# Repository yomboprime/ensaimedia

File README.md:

# Ensaimedia

Ensaimedia permite ver la salida de vídeo de un ZX-Uno o otra FPGA en un ordenador con USB host. Adicionalmente permite redireccionar el teclado, ratón y gamepads del host al ZX-Uno vía puerto serie. La salida de sonido del ZX-Uno también es capturada por el host si dispone de entrada de MIC o de línea de audio. La visualización se realiza desde el navegador web, ya sea en el host, o en otro dispositivo remoto. Por último, permite capturar vídeo y audio a disco.

El desarrollo de este addon ha sido posible gracias a la información y software de Wolfgang Wieser sobre el chip Cypress FX2 [en este sitio web.](https://www.triplespark.net/elec/periph/USB-FX2)

# Índice

En este README:
- [Guía de usuario](https://github.com/yomboprime/ensaimedia#guia-de-usuario-de-ensaimedia)
- [Documentación del protocolo](https://github.com/yomboprime/ensaimedia#documentaci%C3%B3n-ensaimedia)

En este repositorio:
- [Binarios de los cores](https://github.com/yomboprime/ensaimedia/tree/master/cores/)
- [Esquemático y PCB (en formato Kicad)](https://github.com/yomboprime/ensaimedia/tree/master/ensaimediaBoard)
- [Esquemático en formato PDF](https://github.com/yomboprime/ensaimedia/tree/master/ensaimediaBoard/ensaimedia.pdf)
- [Código del servidor](https://github.com/yomboprime/ensaimedia/blob/master/server.js)
- [Código del cliente](https://github.com/yomboprime/ensaimedia/blob/master/client/src/client.js)

# Guia de usuario de Ensaimedia

## Requisitos en el ZX-Uno

Necesitas el addon de Ensaimedia para tu FPGA, así como instalar el core de Ensaimedia de tu máquina retro.

Actualmente sólo está disponible el core oficial de ZX-Uno para ZX Spectrum.

## Requisitos del software Ensaimedia del host:

El host debe ser un sistema Unix, debido a que se usa el programa [fx2pipe](https://www.triplespark.net/elec/periph/USB-FX2/software/fx2pipe.html) para la entrada de vídeo por USB. El cliente (o clientes) puede ser cualquier sistema con un navegador web moderno.

- Ejecuta lo siguiente para instalar los requisitos previos:

`sudo apt install git npm libusb-dev build-essential`

- Pon a tu usuario en el grupo dialout para poder acceder al puerto serie:

`sudo adduser <nombre_de_usuario> dialout`

(Necesitas salir de la sesión o reiniciar para aplicar la adición al grupo, pero puedes reiniciar al terminar la instalación)

## Instalación del software Ensaimedia

Ve al directorio que se desea contenga el directorio de Ensaimedia.

Ejecuta:

```
git clone https://github.com/yomboprime/ensaimedia.git
cd ensaimedia
npm install
```

Adicionalmente hay que instalar unas reglas UDEV. Para ello ejecuta lo siguiente desde el directorio de Ensaimedia:

`sudo cp ./udevrules/z70_usbfx2.rules /etc/udev/rules.d`

Despues reinicia.

## Configuración del software

Edita el fichero `EnsaimediaConfig.json` que está en la raíz de la aplicación:

Como mínimo querrás cambiar el puerto TCP en el que sirve Ensaimedia (opción `listenPort`)

La ruta del fichero del puerto serie se cambia en la opción `serialPortFilePath`.

Si vas a usar audio necesitas primero identificar el dispositivo de audio de tu tarjeta de sonido. Para ello ejecuta:

`arecord -L`

Y verás una lista de dispositivos de entrada de audio. Tendrás que ir probando hasta dar con el mejor; algunos pueden funcionar peor o tener lag.

Copia la primera línea de uno de ellos y pégala (entre comillas) en la opción "audioDevice" en el fichero de configuración.

Para las opciones de guardado a disco mira la sección "Captura a disco" de esta documentación.

## Ejecución de Ensaimedia

Para utilizar Ensaimedia sigue estos pasos:

- Enciende el host.
- Conecta la FPGA al host (ver sección correspondiente más abajo)
- Activa en la FPGA el core deseado de Ensaimedia
- Ejecuta el software de Ensaimedia en el host.

Para ejecutar Ensaimedia sirve una cualquiera de estas tres variantes (en el directorio de Ensaimedia):

- `./Ensaimedia.sh`
- `node server.js`
- `npm start`

Para terminar el programa en cualquier momento, pulsa Ctrl-c en la consola donde lo has abierto.

Al ejecutar verás algunos mensajes indicando los recursos que está abriendo el programa. Si todo va bien, al cabo de un segundo verás el mensaje "New graphic mode: XXXxYYY", que indica que se ha activado el vídeo con esa resolución.

Ahora abre desde un navegador la url: `http://<IP del host>:<puerto TCP configurado>/main.html`

Por ejemplo, si estás abriendo el navegador desde el propio host y el puerto que editaste en `EnsaimediaConfig.json` fue el 12345, abre la url:

`http://127.0.0.1:12345/main.html`

Al abrir la URL ya deberá verse la pantalla de vídeo de la retromáquina.

## Uso de Ensaimedia

El teclado, ratón y dos gamepads funcionan de forma transparente.

Para activar el sonido debes ir al menú, arriba a la derecha (las páginas HTML no permiten reproducción de sonido sin intervención del usuario)

En el menú verás algunas opciones visuales:

- `Pixelated screen`: Hace que los píxels se vean nítidos en vez de interpolados. Nota: De momento no funciona en Firefox.
- `Interlazed`: Mezcla dos fotogramas consecutivos para ver correctamente demos con entrelazado.
- `Resolution is múltiple`: Hace que la resolución de salida sea múltiplo de la nativa de la máquina. Si está desactivada entonces la pantalla se ajusta mejor al espacio disponible pero puede haber píxeles irregulares.
- `Show info on screen`: Muestra en la esquina superior izquierda información de frames por segundo, clientes conectados y audio.
- `Toggle full screen`: Cambia entre modo pantalla completa y ventana.
- `Audio enabled`: Habilita el sonido.
- `Input options`: Aqui puedes activar o desactivar el envío de eventos de teclado, ratón y gamepads.
- `Open/close Controls`: Minimiza o expande el menú.

## Captura a disco

Para activar la captura a disco, establece a `true` los valores `saveVideoToDiskEnabled` y/o `saveAudioToDiskEnabled` en el fichero de configuración `EnsaimediaConfig.json`.

La captura se realiza en el host, los clientes del navegador no pueden afectar a esta.

La captura comenzará tan pronto como haya señal de vídeo, y la sesión se guardará en una carpeta nueva bajo `Ensaimedia/savedSessions/` (con nombre dependiente de la fecha y hora) como dos ficheros: `video.bin` con el vídeo en raw, y `audio.wav` con el audio. Estos ficheros continuarán creciendo mientras esté funcionando el programa, a un ritmo aproximado de 500 MB por minuto (para el core de ZX Spectrum con vídeo y audio).

Tras finalizar la sesión de Ensaimedia hay que postprocesar los datos raw para generar un vídeo comprimido webm "píxel perfect" que se pueda reproducir. Este proceso puede tardar 10 veces lo que dura el vídeo. Para ello:

- Abre un terminal de consola en la carpeta de Ensaimedia
- Ejecuta la orden `node convertCapture.js <carpeta> ni FPS`, donde:
	- `<carpeta>` es el nombre de la subcarpeta bajo `savedSessions`, sin barras.
	- `ni` Significa "not interlazed". Pon `i` en su lugar si quieres que se mezclen fotogramas dos a dos para desentrelazar el vídeo (el vídeo de salida tendrá la mitad de FPS)
	- FPS son los FPS originales del vídeo, 50 para el core de  ZX Spectrum. Puede contener decimales. El valor es independiente de si seleccionas entrelazado o no.

Este proceso convierte el vídeo raw a imágenes `.png` que ocupan otro tanto, y después llama al programa `ffmpeg` para crear el vídeo webm. En todo momento se muestra el estado de la conversión.

Al terminar se habrá creado el fichero `video.webm` en la subcarpeta de la sesión. Puedes entonces borrar el resto de ficheros. Puedes volver a crear el vídeo en cualquier momento si los ficheros `video.bin` y `audio.wav` están presentes (el fichero de audio es opcional)

## Conexión del ZX-Uno al host

Hay tres conexiones por cable entre el host y la FPGA: Un cable microUSB para el vídeo, un puerto serie para periféricos y RTC, y el cable de audio analógico.

Muy importante (Sólo para ZX-Uno): No conectes el microUSB de alimentación normal del ZX-Uno mientras usas el addon de Ensaimedia. Tanto el ZX-Uno como el addon son alimentados por el cable microUSB de éste último.

### Cable MicroUSB

Este cable conecta el host a la FPGA mediante un cable microUSB con líneas de datos (hay cables que sólo sirven para cargar y no tienen los cables que transportan los datos, sólo los de alimentación)

Este cable alimenta al ZX-Uno y al addon.

Es importante que el puerto del host sea USB 2.0 o superior. No sirve USB 1.0 ó 1.1.

### Cable puerto serie

Si el host tiene puerto serie de 3.3V accesible, puedes conectarlo directamente con tres cables Dupont (los comunes de 2.54 mm de separación). Si no, necesitarás un dongle USB Serial **que tenga jumper para configurarse a 3.3V (5V no vale)** y ocupar un puerto USB más.

La conexión de los tres cables Dupont en cualquier caso es la siguiente (verás el conector en el addon indicado como "serial" y los pines "RX", "TX" y "GND":

```
RX de la FPGA <--- TX del dongle
TX de la FPGA ---> RX del dongle
GND de la FPGA --- GND del dongle
```

### Cable de audio

Es un simple cable de audio estéreo minijack macho-macho. Se conecta desde la salida de sonido de la FPGA a la entrada de mic o de línea en el host.

Puede que necesites usar alsamixer para ajustar el volumen de la entrada.

## Problemas conocidos

En el propio host y en red local (LAN) el sonido funciona bien. Sin embargo, debido a que se usa WebRTC, para usar el sonido en Ensaimedia desde dispositivos que no tienen una IP pública (o si el host no tiene IP pública) habría que usar un "TURN server". No se ha implementado aún esta posibilidad, al no existir servidores TURN de acceso público.

-------------------------------------

# Documentación Ensaimedia

Ensaimedia consiste en una interfaz de comunicación entre un ZX-Uno (o otra FPGA) y un host USB mediante USB 2.0, para transmisión de vídeo al host, además de una interfaz serie (UART) para transmitir información de periféricos desde el host al ZX-Uno. Adicionalmente el software del host permite entrada y salida de audio analógico, conectando LINE y EAR del ZX-Uno a MIC y LINE del host.

Esto permite:

- Usar la salida HDMI del host (o cualquier salida futura) como nativa del core de ZX-Uno.
- Usar periféricos USB en el host como entrada en el ZX-Uno: Teclado, ratón y gamepads.
- Virtualizar completamente el ZX-Uno y hacerlo disponible a clientes web, cada uno con sus periféricos y recepción de vídeo y audio.
- Capturar a disco la sesión de vídeo y audio.

Las salidas de vídeo nativas así como los periféricos nativos del ZX-Uno se pueden usar a la vez que Ensaimedia, o bien se pueden dejar desconectados.

# Interfaz física de Ensaimedia

## Interfaz de vídeo

La interfaz de vídeo en Ensaimedia 1.0 consiste en un bus síncrono en el que el ZX-Uno es el master, y un chip Cypress CY7C68013A-56PVXC (FX2LP) lee ese bus y envía los datos por USB 2.0.

El bus es de 16 bits de ancho. El máximo ancho de banda teórico del bus es 48 MHz * 2 = 96 Mbytes/s. Pero el máximo transferible por USB 2.0 es aproximadamente 42 Mbytes/s, usando el programa [fx2pipe](https://www.triplespark.net/elec/periph/USB-FX2/software/fx2pipe.html), qué solo permite transmitir en una dirección. Otros drivers/librerías permiten transferencia bidireccional pero con menos ancho de banda.

Las señales de control del bus son (out es en dirección al host, in es en dirección al ZX-Uno):

- SLCLK (out) Reloj del bus síncrono proporcionado por el core del ZX-Uno. Debe estar entre 5 y 48 MHz y ser estable.
- SLWR (out) Señal de escritura (de un word de 16 bits) al bus (El ZX-Uno escribe)
- SLRD (out) Señal de lectura desde el bus (El ZX-Uno lee) (*)
- AVAILABLE (in): Pin que indica que hay un word disponible para lectura para el ZX-Uno. (*)

(*) Esta capacidad es posible en el addon de ZX-Uno Ensaimedia 1.0, pero no es usada por el sistema Ensaimedia para la salida de vídeo. Otros cores/experimentos pueden hacer uso de ella. Para conseguir dirección de datos desde el host a la FPGA en ensaimedia 1.0 se debe cambiar el "solder jumper" J8 a GND (pin 1 de J8). Para uso de ensaimedia debe estar a 3V3 (pin 3 de J8) El pin del FX2 en concreto es ADDR1: Dirección específica del FX2LP (número de endpoint). Es decir, este bit debe valer 1 para dirección de transmisión del ZX-Uno al host, y 0 para la dirección contraria.

## Interfaz serie

La interfaz serie para periféricos entre el ZX-Uno y el host USB es una UART estándar a 3.3V y 115200 baudios, 8 bits de datos, 1 bit stop, sin paridad ni control de flujo. Se usan ambos pines RX y TX.

# Protocolo Ensaimedia

## Formato de video de Ensaimedia

El ZX-Uno transmite al host comandos completos que son palabras de 16 bits de ancho. Estos comandos especifican el formato de vídeo y transfieren los valores RGB de los píxels.

Los comandos X_RES, Y_RES, MODE, START_FRAME y PIXEL son obligatorios en cada frame.

### Comando: PIXEL

Especifica un pixel según el formato seleccionado (ver comando MODE)

Según el formato de pixel seleccionado, cada pixel pueden estar dividido en varios comandos (words) diferentes.

### Comando: START_FRAME

1000000000000000 : marca de inicio de frame. El host espera un frame completo (dos START_FRAME) antes de comenzar a procesar el vídeo y darlo como válido.

### Comando: X_RES

101XXXXXXXXXXXXX : ajustar resolucion horizontal a X + 1 (X es de 13 bits, resolución desde 1 pixel hasta 8K pixels). Aplica en el siguiente inicio de frame.

### Comando: Y_RES

110YYYYYYYYYYYYY : ajustar resolucion vertical a Y + 1 (X es de 13 bits, resolución desde 1 pixel hasta 8K pixels) Aplica en el siguiente inicio de frame.

### Comando: MODE

111xxxxxmmmmRRFF : Establecer modo de pixel, reflexión (flip) y posterior rotación.

- m:
	- 0000: modo Spectrum ZX-Uno R3G3B3.
		- Formato del comando de pixel (1 word): 16'b0000000RRRGGGBBB
	- 0001: modo R5G5B5.
		- Formato del comando de pixel (1 word): 16'b0RRRRRGGGGGBBBBB
	- 0010: modo R8G8B8.
		- Formato del comando de pixel (2 words): 16'b0000GGGGRRRRRRRR, 16'b0001GGGGBBBBBBBB.
		- El primer word contiene el nibble de mayor peso del canal G.
	- 0011: modo R8G8B8.
		- Formato del comando de pixel (3 words): 16'b00000000RRRRRRRR, 16'b00000001GGGGGGGG, 16'b00000010BBBBBBBB
	- Otros valores: No definido aún

- x: reservado para futuros usos según el valor de m.

- FF = Reflexión: 00 no reflexión, 01 reflexion horizontal, 10 vertical, 11 ambas.

- RR = Rotación: 00 normal, 01 = 90 grados sentido horario, 10 = 180 grados, 11 = 270 grados

Notas:

La rotación de la imagen se aplica después de la reflexión.

Este comando aplica en el siguiente inicio de frame.

Múltiples comandos MODE son posibles en un mismo frame, según futuros usos.

## Formato de transmisión de los periféricos de Ensaimedia

Ensaimedia puede aunar diferentes periféricos de entrada de varios usuarios online (además de los del host) en una sola interfaz serie.

Los periféricos que provee la interfaz de Ensaimedia son:

- Un teclado PS/2
- Un ratón PS/2 con tres botones (sin rueda)
- Dos joysticks digitales de cuatro direcciones y 8 botones cada uno

En el core de ZX Spectrum no están implementados, sencillamente por no haber: el tercer botón del ratón, ni el segundo joystick con sus botones. Y el primer joystick sólo tiene dos botones.

Una transmisión completa consiste en una trama desde el host al ZX-Uno, y otra trama de respuesta desde el ZX-Uno al host. Este ciclo se repite a disposición del host.

### Trama Host -> ZX-Uno:

La secuencia de bytes de la trama es:

- 0x34: Inicio de frame
- 1 byte de configuración
- 1 byte joyDir: udlrudlr JoyUp1, JoyDown1, JoyLeft1, JoyRight1, JoyUp2, JoyDown2, JoyLeft2, JoyRight2
- 1 byte joyBtn1: 8 botones del Joystick1
- 1 byte joyBtn2: 8 botones del Joystick2
- 1 byte numBytesKeyb:  Num. bytes de PS2 de teclado. Si no hay, a 0. Max 255
- 1 byte numBytesMouse:  Num. bytes de PS2 de ratón. Si no hay, a 0. Max 255
- bytes de teclado, si los hay
- bytes de ratón, si los hay
- bytes de fecha y hora. Si el Formato es 0: No hay bytes de fecha y hora. Formato 1: 16 bytes; Formato 2: 8 bytes. Formato 3: variable, terminado en el byte 0x00.

#### Byte de configuración

011000ff

- ff: Formato de fecha y hora (0 al 3) en esta trama. Otros formatos de hora diferentes al deseado por el ZX-Uno serán ignorados por éste.

Otros valores del byte son reservados.

#### Formatos de fecha y hora:

Ensaimedia implementa un módulo de tiempo real o RTC. El host envía el tiempo cada segundo, pudiéndose transmitir en varios formatos. En el core de Spectrum del ZX-Uno el módulo se traduce en la implementación de los puertos del addon RTC del DivMMC. Hay que tener en cuenta que este addon no implementa husos horarios, por lo que siempre se mostrará la hora UTC para compatibilizar la hora de los ficheros en sistemas de almacenamiento modernos. El puerto usado para el RTC en el core Spectrum es el 0xCXEF (X = don't care)

Los formatos de fecha y hora posibles son:

- Formato 0: No hay fecha y hora (valor por defecto al empezar la transmisión)

- Formato 1: Formato del chip RTC242X (addon DivMMC)

	16 bytes con los valores de los registros del chip.

	Nota: Los días de la semana del 0 al 6 empiezan en Domingo.

	Ver datasheet del chip para más información.

- Formato 2: Timestamp

	8 bytes con un entero de 64 bits sin signo (more significant byte first) con los milisegundos transcurridos desde 00:00:00 UTC del 1 de enero de 1970.

- Formato 3: Formato flexible de usuario.

	En este formato se transmite una cadena de bytes de longitud arbitraria y formato definido por el usuario, y terminada en el byte 0.

	Lo que se haga con esa cadena en el core de ZX-Uno depende del core concreto. El comportamiento por defecto es leer la cadena e ignorarla.

### Respuesta del ZX-Uno al host: byte de ack

101000ff

ff: Formato de hora deseado, 0 al 3 (para las próximas tramas)

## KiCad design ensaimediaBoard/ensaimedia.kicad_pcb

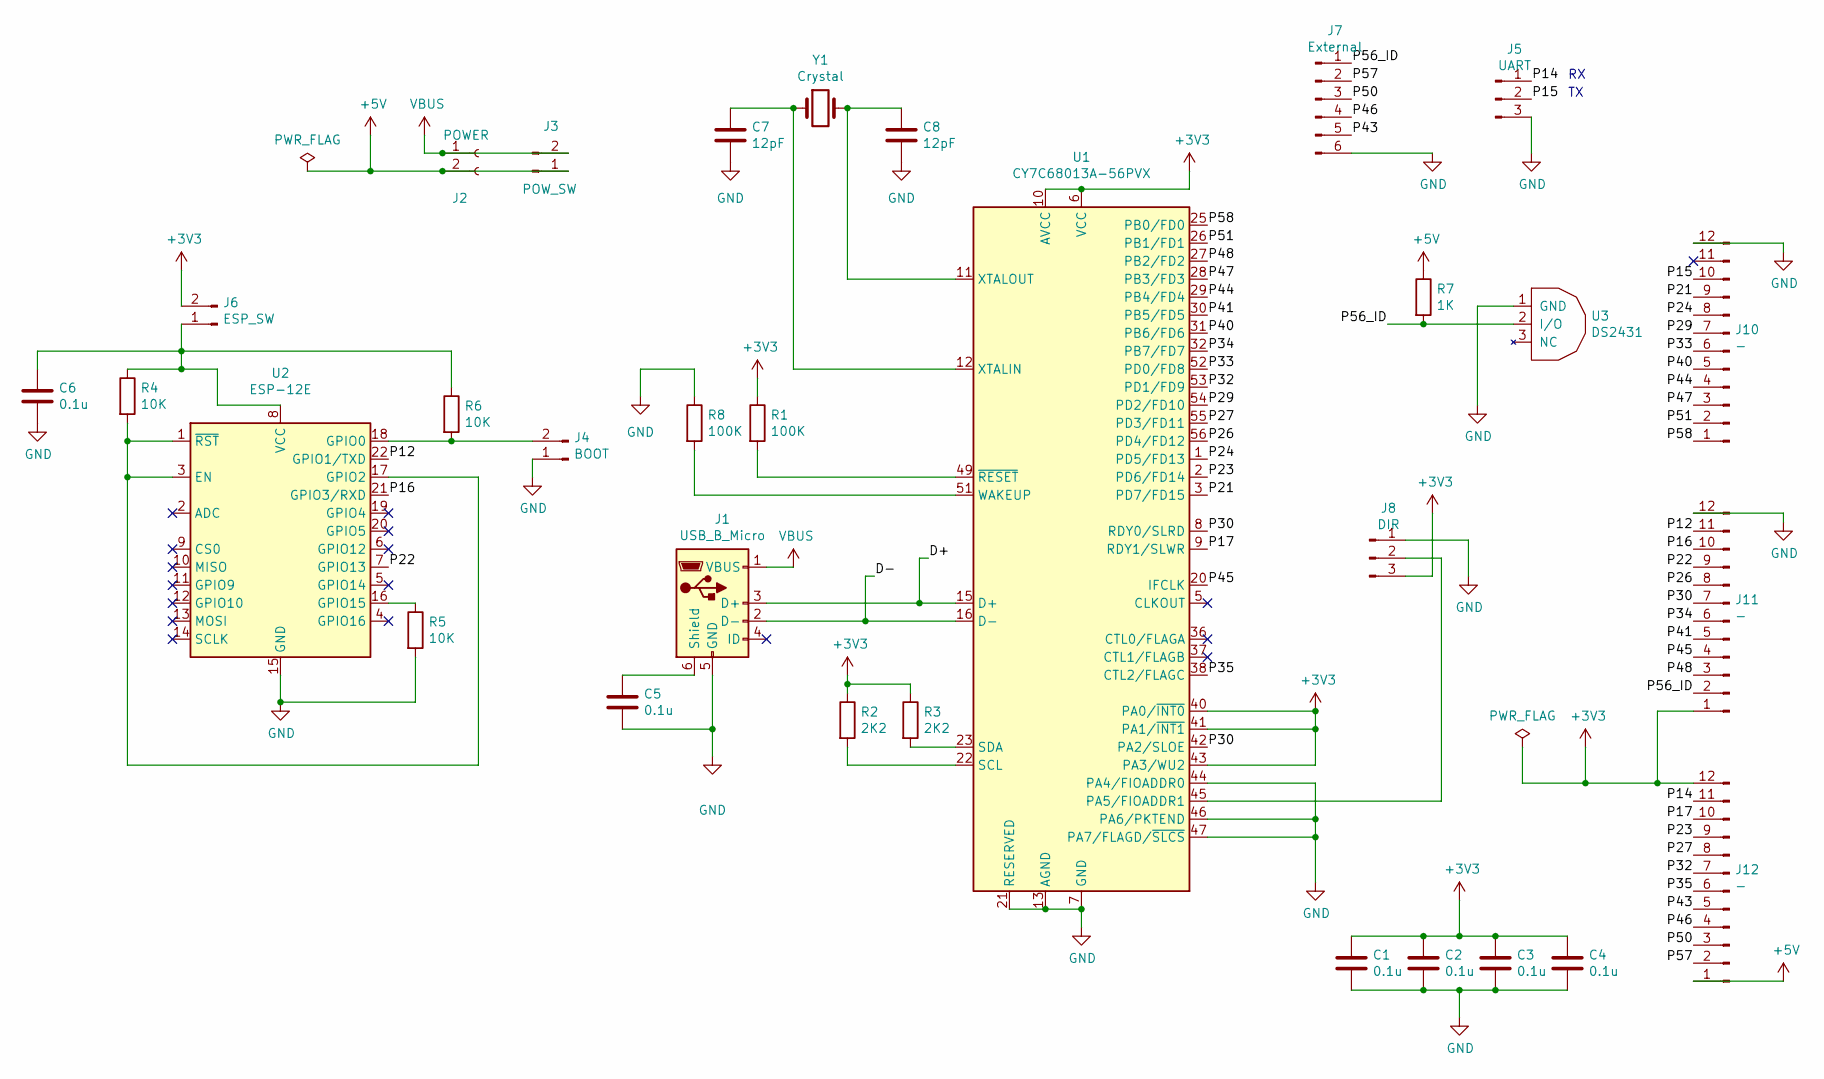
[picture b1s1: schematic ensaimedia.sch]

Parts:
C1, C2, C3, C4, C5, C6: 0.1u; C_0805_2012Metric_Pad1.15x1.40mm_HandSolder
C7, C8: 12pF; C_0805_2012Metric_Pad1.15x1.40mm_HandSolder
J1: USB_B_Micro; USB_Micro-B_Wuerth_629105150521_CircularHoles
J2: POWER; PinHeader_1x02_P2.54mm_Vertical
J3: POW_SW; PinHeader_1x02_P2.54mm_Horizontal
J4: BOOT; PinHeader_1x02_P2.54mm_Vertical
J5: UART; PinHeader_1x03_P2.54mm_Vertical
J6: ESP_SW; PinHeader_1x02_P2.54mm_Vertical
J7: External; PinHeader_1x06_P2.54mm_Vertical
J8: DIR; SolderJumper-3_P1.3mm_Open_RoundedPad1.0x1.5mm
J10, J11, J12: -; PinHeader_1x12_P2.54mm_Vertical
R1, R8: 100K; R_0805_2012Metric_Pad1.15x1.40mm_HandSolder
R2, R3: 2K2; R_0805_2012Metric_Pad1.15x1.40mm_HandSolder
R4, R5, R6: 10K; R_0805_2012Metric_Pad1.15x1.40mm_HandSolder
R7: 1K; R_0805_2012Metric_Pad1.15x1.40mm_HandSolder
U1: CY7C68013A-56PVX; SSOP-56_7.5x18.5mm_P0.635mm
U2: ESP-12E
U3: DS2431; TO-92_Inline
Y1: Crystal; Crystal_HC49-U_Vertical

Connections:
+3V3: C1.1, C2.1, C3.1, C4.1, J6.2, J8.3, J11.1, J12.12, R1.1, R2.1, R3.1, U1.6 (VCC), U1.10 (AVCC), U1.14 (AVCC), U1.18 (VCC), U1.24 (VCC), U1.34 (VCC), U1.39 (VCC), U1.40 (PA0/~INT0), U1.41 (PA1/~INT1), U1.43 (PA3/WU2), U1.50 (VCC)
+5V: J2.2, J3.1, J12.1, R7.1
/D+: J1.3 (D+), U1.15 (D+)
/D-: J1.2 (D-), U1.16 (D-)
/P12: J11.11, U2.22 (GPIO1/TXD)
/P14: J5.1, J12.11
/P15: J5.2, J10.10
/P16: J11.10, U2.21 (GPIO3/RXD)
/P17: J12.10, U1.9 (RDY1/SLWR)
/P21: J10.9, U1.3 (PD7/FD15)
/P22: J11.9, U2.7 (GPIO13)
/P23: J12.9, U1.2 (PD6/FD14)
/P24: J10.8, U1.1 (PD5/FD13)
/P26: J11.8, U1.56 (PD4/FD12)
/P27: J12.8, U1.55 (PD3/FD11)
/P29: J10.7, U1.54 (PD2/FD10)
/P30: J11.7, U1.8 (RDY0/SLRD), U1.42 (PA2/SLOE)
/P32: J12.7, U1.53 (PD1/FD9)
/P33: J10.6, U1.52 (PD0/FD8)
/P34: J11.6, U1.32 (PB7/FD7)
/P35: J12.6, U1.38 (CTL2/FLAGC)
/P40: J10.5, U1.31 (PB6/FD6)
/P41: J11.5, U1.30 (PB5/FD5)
/P43: J7.5, J12.5
/P44: J10.4, U1.29 (PB4/FD4)
/P45: J11.4, U1.20 (IFCLK)
/P46: J7.4, J12.4
/P47: J10.3, U1.28 (PB3/FD3)
/P48: J11.3, U1.27 (PB2/FD2)
/P50: J7.3, J12.3
/P51: J10.2, U1.26 (PB1/FD1)
/P56_ID: J7.1, J11.2, R7.2, U3.2 (I/O)
/P57: J7.2, J12.2
/P58: J10.1, U1.25 (PB0/FD0)
GND: C1.2, C2.2, C3.2, C4.2, C5.2, C6.2, C7.2, C8.2, J1.5 (GND), J4.1, J5.3, J7.6, J8.1, J10.12, J11.12, R5.2, R8.1, U1.4 (GND), U1.7 (GND), U1.13 (AGND), U1.17 (AGND), U1.19 (GND), U1.21 (RESERVED), U1.33 (GND), U1.35 (GND), U1.44 (PA4/FIOADDR0), U1.46 (PA6/PKTEND), U1.47 (PA7/FLAGD/~SLCS), U1.48 (GND), U2.15 (GND), U3.1 (GND)
unnamed: C5.1, J1.6 (Shield)
unnamed: C6.1, J6.1, R4.1, R6.1, U2.8 (VCC)
unnamed: C7.1, U1.12 (XTALIN), Y1.1
unnamed: C8.1, U1.11 (XTALOUT), Y1.2
unnamed: J4.2, R6.2, U2.18 (GPIO0)
unnamed: J8.2, U1.45 (PA5/FIOADDR1)
unnamed: R1.2, U1.49 (~RESET)
unnamed: R2.2, U1.22 (SCL)
unnamed: R3.2, U1.23 (SDA)
unnamed: R4.2, U2.1 (~RST), U2.3 (EN), U2.17 (GPIO2)
unnamed: R5.1, U2.16 (GPIO15)
unnamed: R8.2, U1.51 (WAKEUP)
VBUS: J1.1 (VBUS), J2.1, J3.2

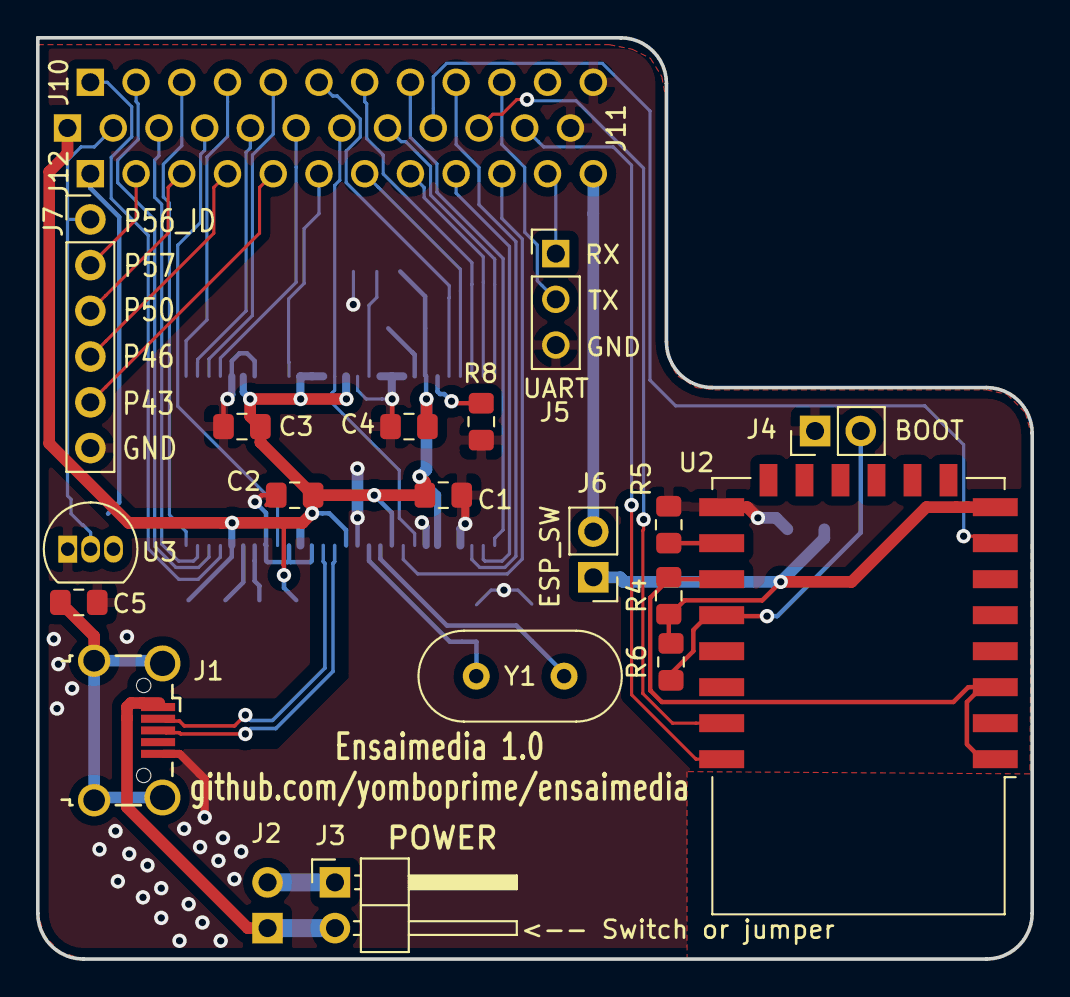
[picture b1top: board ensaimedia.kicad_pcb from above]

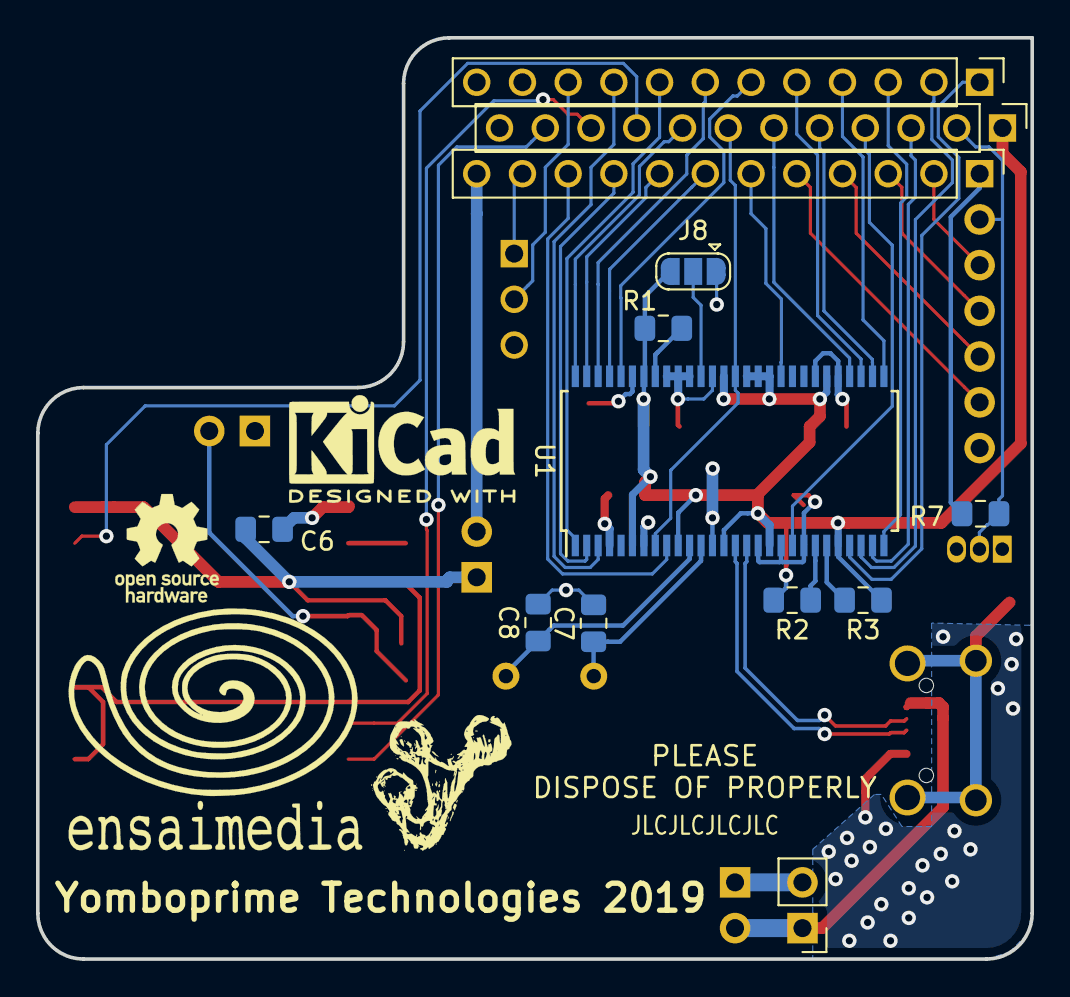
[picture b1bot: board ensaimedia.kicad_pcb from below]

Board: 2 copper layers, 55.2 x 51.2 mm, 31 parts (13 on the bottom side), 48 nets.

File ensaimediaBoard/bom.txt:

BOM Ensaimedia 1.0

Componentes principales:

U1						CY7C68013A-56PVX
C1, C2, C3, C4, C5		0.1 uF 0805 decoupling caps
Y1						24 MHz crystal HC-49S
C7, C8					12 pF caps 0805
R1, R8					100 KOhm 0805
R2, R3					2.2 KOhm 0805
J1						MicroUSB Werth connector
J10, J11, J12			10p 2.54mm male pin headers
J2						2p 2.54mm female pin header
J3						2p 2.54mm male pin header OR Switch


EEPROM (opcional):

U3						DS2431 1-Wire EEPROM
R7						1 KOhm 0805


Componentes del WiFi (opcional):

U2						ESP-12E
R4, R5, R6				10 KOhm 0805
C6						0.1 uF 0805 decoupling cap
J4						2p 2.54mm male pin header OR Switch

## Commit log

2019-10-23 Fix typo
2019-10-25 Add DIR solder jumper comment in the schematic.
2019-10-25 Correcciones al readme
2019-10-25 Adición de índice al readme
2019-10-25 Adiciones readme. Añadir esquemático en PDF
2019-10-30 Update readme index
2019-10-30 Fix readme index
2019-10-30 Fix readme
2019-10-30 Fix readme bis
2019-11-04 Cambiado pinout del core a la última versión de la PCB.
2019-11-04 Añadido comentario sobre el modo fundamental del cristal usado
2019-11-05 Añadidos screenshots
2019-11-05 Corregidos SVGs
2019-11-05 Corregidos SVGs bis
2019-11-06 Añadido comentario en README sobre salidas y periféricos nativos
